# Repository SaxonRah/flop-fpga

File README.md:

# New lead - 50 pin Centronics NEC98: 5.25" 1.2Mb external drive / DB25 5.25" 1.2Mb external drive 
It's claimed that windows 7/10/11 legacy drivers exist from DOS/Windows for an external 5.25" drive. I know the 5.25" external drives exist with a DB25, such as CMS Enhancements External 1.2MB Floppy Drive EF-360, but never thought they would work in Windows and still doubt that they do.

In addition, the PC-9800 series has external 5.25" drives, both dual (AD-F51W, CRC-FD5WS-1, FDD-5WN, ID-5W, LDSK-5, LFD-52, LFD-582F, PC-9831-MF2, PC-FD512R) and single drive (AD-F51SR, CRC-FD5SS, FD-51, FDC-57AUTO, FDD-5SN, ID-5S?, LFD-51, LFD-581F, PC-FD511R, TF511), i think these are all 50 pin centronics and not db25 though. Also require something like a NEC floppy board (PC-9801-xxx), CRC-FDC3, FDD-1M, FDD-1MZ, FDD-1X, or FDD-1MX to run i would suspect. It's where i think this driver, if it exists stems from originally.. When DOS was competing with CP/M, NEC was able to dominate the Japanese market with DOS and ultimately resulted in said driver for Windows 2000 / NT 4.0.

If this 5.25" driver exists and it was on Win2k and or NT 4.0 on some PC-98 system, then XP should have the legacy driver and another pathway would be potentially open for a 5.25" on modern OS via reverse engineering the connection from the PC-98 motherboard (PC-98's C-BUS) to the 50 pin to 50 pin Centronics cable to the internal 34 pin connection on the drive in the external 5.25" floppy enclosures.

fd50to34 https://gitlab.com/NF6X_Retrocomputing/fd50to34 can be used in reverse. ie 34 to 50 pin. possibly useful information.

c-bus https://www.reddit.com/r/pc98/wiki/c-bus/

# uuuhh info from some dead japanese site about the floppy driver
Drive12EMedia120Nec98,                 //  5.25" 1.2Mb externel drive; 1.2Mb   media

Drive12EMedia123Nec98,                 //  5.25" 1.2Mb externel drive; 1.25Mb   media

MediaType; StepRateHeadUnloadTime; HeadLoadTime; MotorOffTime; SectorLengthCode; BytesPerSector; SectorsPerTrack; ReadWriteGapLength; FormatGapLength; FormatFillCharacter; HeadSettleTime; MotorSettleTimeRead; MotorSettleTimeWrite; MaximumTrack; CylinderShift; DataTransferRate; NumberOfHeads; DataLength; MediaByte; SkewDelta; 

all UCHAR except USHORT (BytesPerSector, MotorSettleTimeRead, MotorSettleTimeWrite)

// 5.25" 1.2Mb externel drive

{ F5_1Pt2_512,    0xbf, 0x32, 0x25, 0x2, 0x200, 0x0f, 0x1b, 0x54, 0xe5, 0xf, 1000, 1000, 0x4f, 0, 0x0, 0x2, 0xff, 0xf9, 0 }

{ F5_1Pt23_1024,  0xbf, 0x32, 0x25, 0x3, 0x400, 0x08, 0x35, 0x74, 0xe5, 0xf, 1000, 1000, 0x4c, 0, 0x0, 0x2, 0xff, 0xfe, 0 }

// 5.25" 1.2Mb drive

{ F5_1Pt2_512,  0xcf, 0x24, 0x25, 0x2, 0x200, 0x0f, 0x1b, 0x54, 0xe5, 0xf, 1000, 1000, 0x4f, 0, 0x0, 0x2, 0xff, 0xf9, 0 }

{ F5_1Pt23_1024,0xcf, 0x24, 0x25, 0x3, 0x400, 0x08, 0x35, 0x74, 0xe5, 0xf, 1000, 1000, 0x4c, 0, 0x0, 0x2, 0xff, 0xfe, 0 }

Google Translated
    // This file includes data and hardware declarations for the NEC PD765 (aka AT, ISA, and ix86) and Intel 82077 (aka MIPS) floppy driver for NT.

# IBM 4869 External 5.25” Floppy Disk Drive with Parallel RS449 (37 pin) 
pathway?

# PCIe Floppy Drive Controller
After extensive research on PCIe, it simply isn't possible to have a floppy controller on pcie without custom software. Custom software would render a PCIe floppy controller useless as it would act like a usb floppy and not a native floppy drive connected to the motherboard. The native connection to the CPU is needed to take advantage of the pre-existing windows 7 - windows 11 5.25" floppy drivers, these original windows drivers are needed for omniflop to replace. 

# Ideally omniflop and or fluxengine software would be used by the owner of said device.
The only way I can see a 5.25" working on modern windows is an industrial motherboard and potentially the dISApointment mod using the TPM headers containing the LPC bus. Which most mobos likely require a bodge wire modification. Some can be simple, some can be difficult.

A motherboard with a working dISApointment mod might allow for a Monster FDC 8 Port ISA Floppy Controller, or Quad-Flop – 4 Port ISA Floppy Controller.

Maybe, just maybe, a consumer modern motherboard with winblows will be able to talk to 5.25" and 3.5" disks over the omniflop driver via ISA through LPC bridged to eSPI.

# ISA through LPC bridged to eSPI

# LPC Spec
Some mobos have ECE1200, W83626F, or F85226A, other chips too support LPC 1.1, which is the full ISA support, however the higher clocked ISA bus can have problems with slower clocked ISA cards. 

Some mobos only have the slower ISA bus supported on LPC.

# Skylake+ cannot support LPC over TPM anymore because of architecture changes which resulted in chipset modifcation over to eSPI.
https://web.archive.org/web/20230927192809/https://community.intel.com/t5/Embedded-Intel-Core-Processors/Anybody-to-know-why-Intel-change-LPC-bus-clock-from-33MHz-to/td-p/652673

# Skylake+ might still support LPC if mobo has chips for eSPI to LPC
ECE1200 eSPI-to-LPC chip. "ECE1200 is a device designed to implement a Bridge function from an eSPI-configured Intel Chipset to a legacy downstream system, providing Master interfaces for an LPC bus, Serial IRQ and CLKRUN# features."
https://www.mouser.com/ProductDetail/Microchip-Technology/ECE1200-I-LD?qs=T3oQrply3y%2FOHml1lyLW5w%3D%3D

EV22J81A is the ECE1200 eSPI-to-LPC dev board, raw chips cost around 4 USD

F85227N eSPI to LPC bridge chip.

# most modern LPC supported mobo i could find 
Asrock B650 LiveMixer motherboard - has special addon card (not released) that takes advantage of the eSPI/LPC bus to extend the motherboard and uses a NCT6686D chip on the mobo to supply LPC to eSPI.
The Asrock X670E Taichi mobo also has a NCT6686D paired with NCT6796D Nuvoton LPC/eSPI SI/O

# PICMG 1.3
PICMG 1.3 host cards sometimes have eSPI with LPC support via bridge chip.

# Existance of POST Code Card for eSPI interface
This to me reinforces the idea that a 5.25" floppy controller should be possible via eSPI to LPC bridge to ISA or LPC supported motherboard to ISA.

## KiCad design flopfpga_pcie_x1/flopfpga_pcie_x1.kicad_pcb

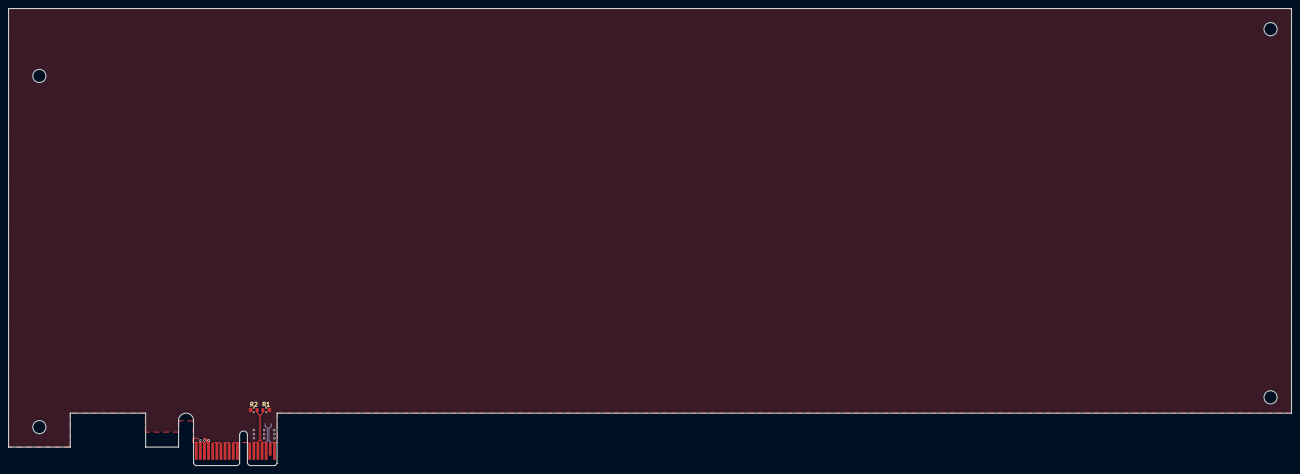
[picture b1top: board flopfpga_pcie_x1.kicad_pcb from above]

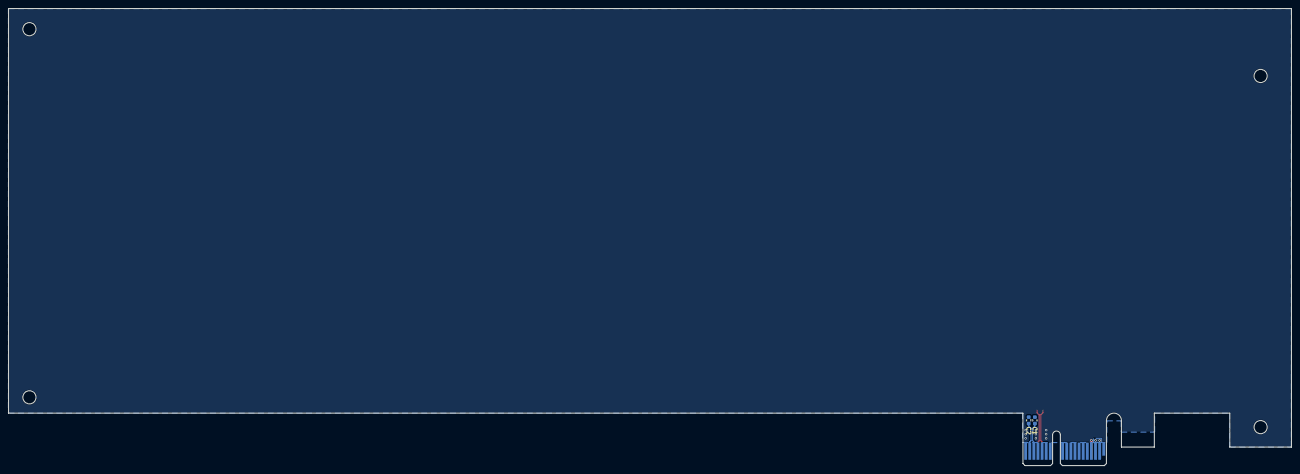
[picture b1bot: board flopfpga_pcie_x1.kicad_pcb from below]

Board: 4 copper layers, 312.0 x 111.2 mm, 6 parts (2 on the bottom side), 7 nets.

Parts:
C1, C2: 100n; C_0603_1608Metric
J1: PCIexpress_bracket; PCIexpress_bracket_full
J2: PCIexpress_x1
R1, R2: 49.9; R_0603_1608Metric

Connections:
+3V3: J2.A9, J2.A10, J2.B8
+12V: J2.A2, J2.A3, J2.B1, J2.B2, J2.B3
/PCIexpress_connector/_PER0_N: C2.1, J2.A17
/PCIexpress_connector/_PER0_P: C1.2, J2.A16
/PET0_N: J2.B15, R1.1
/PET0_P: J2.B14, R2.1
GND: J2.A4, J2.A12, J2.A15, J2.A18, J2.B4, J2.B7, J2.B13, J2.B16, J2.B18, R1.2, R2.2

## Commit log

2024-01-21 Create FiveTwoFiveFloppyController.v
    5.25" 5 1/4 floppy controller example
2024-01-21 Create PCIeFloppyController.v
    PCIe floppy controller example
2024-01-21 Create win_driver.cpp
    example driver for FPGA 5.25" Floppy Controller
2024-01-25 Add files via upload
    added pcie x1 kicad template,
2024-01-26 Delete flopfpga_pcie_x1 directory
    pcie floppy controller != native floppy
